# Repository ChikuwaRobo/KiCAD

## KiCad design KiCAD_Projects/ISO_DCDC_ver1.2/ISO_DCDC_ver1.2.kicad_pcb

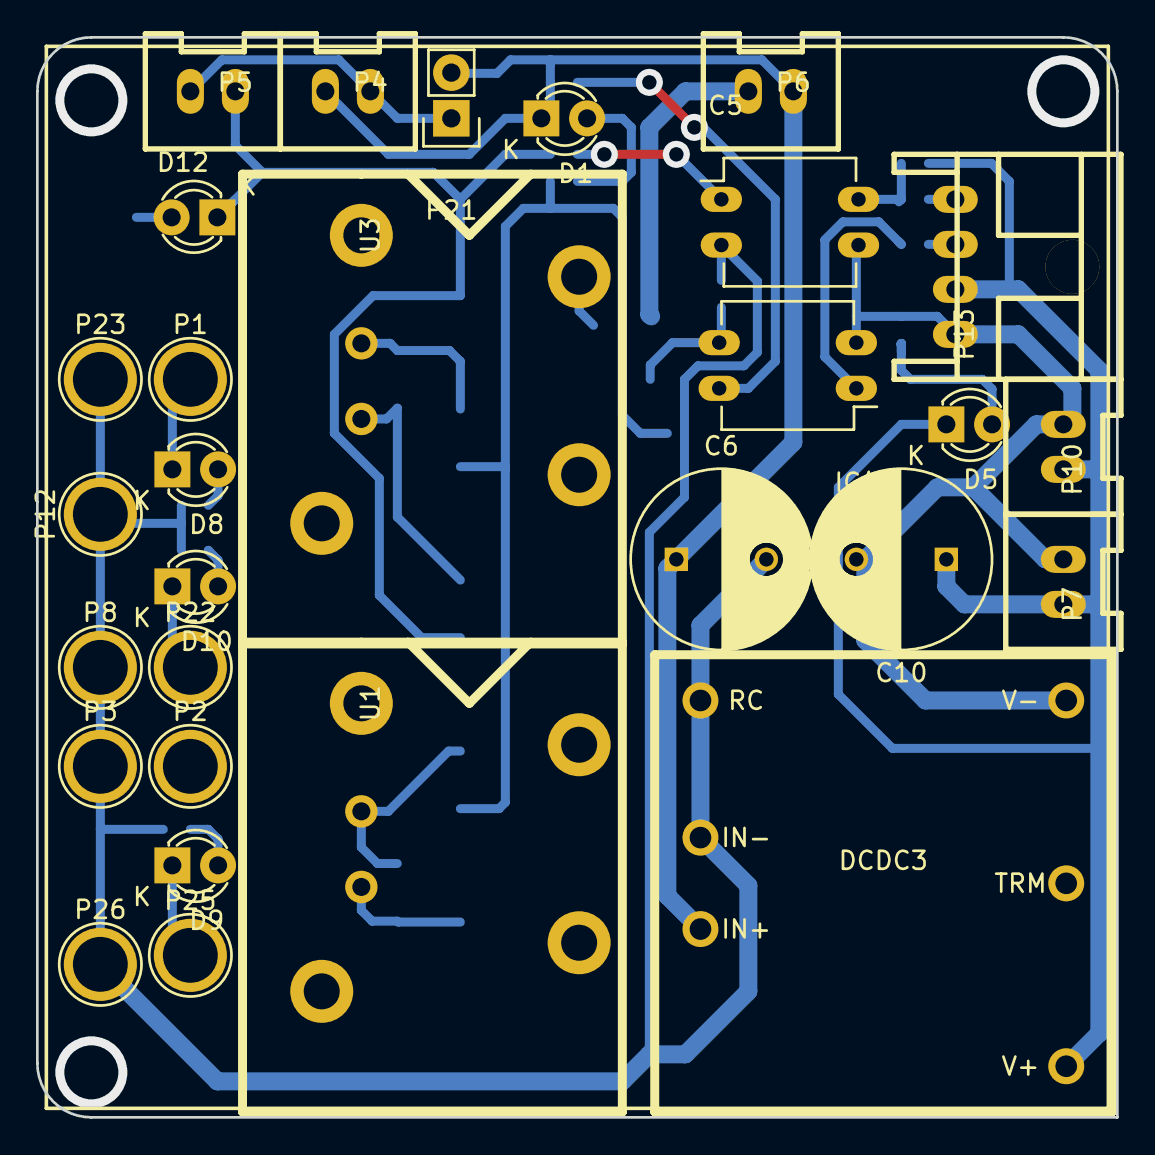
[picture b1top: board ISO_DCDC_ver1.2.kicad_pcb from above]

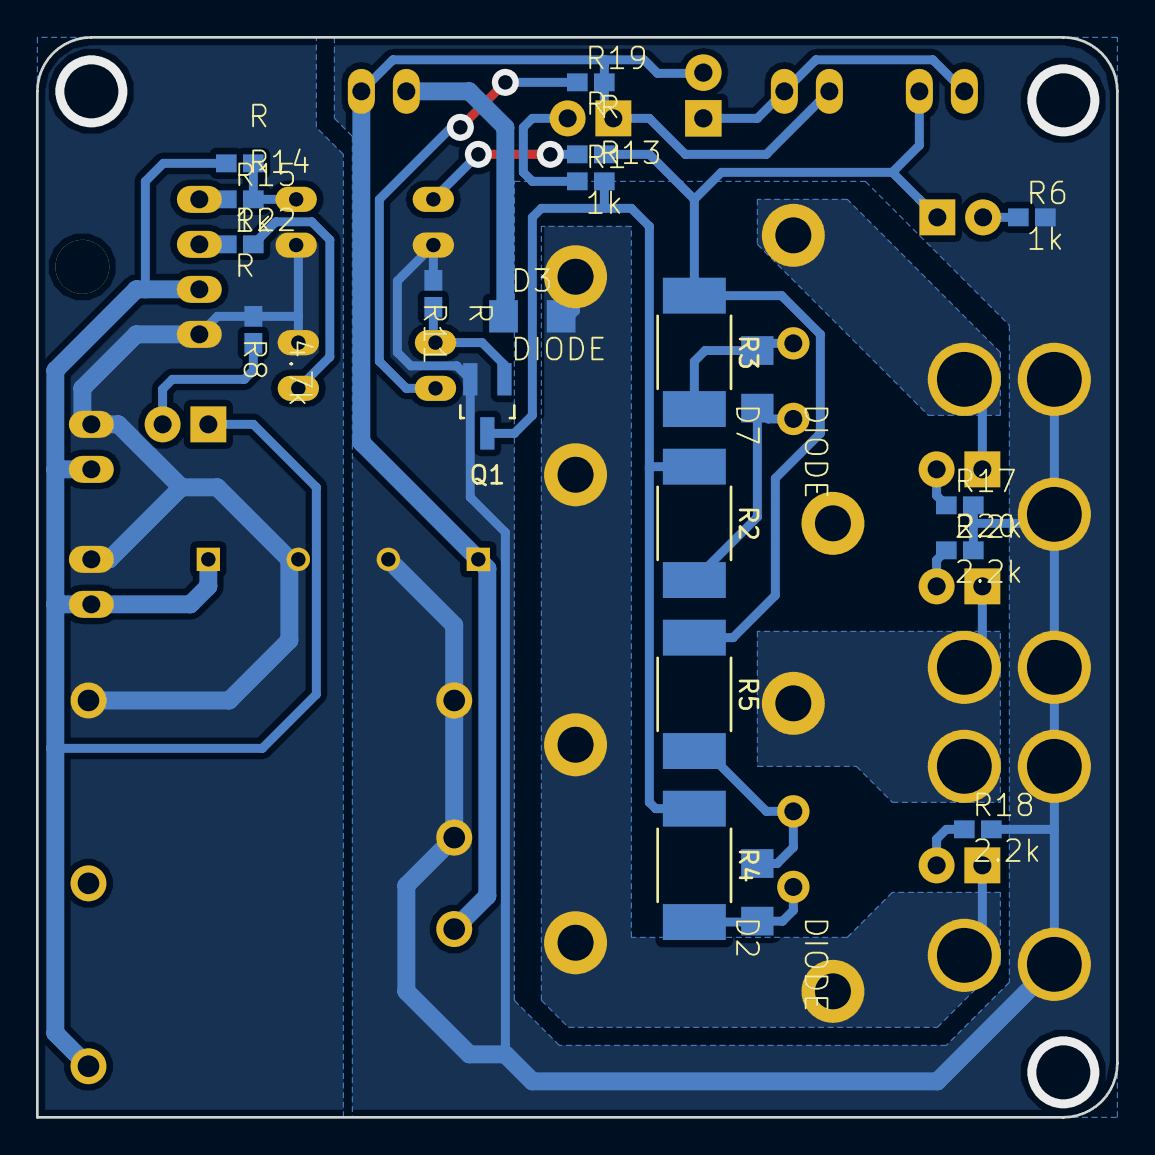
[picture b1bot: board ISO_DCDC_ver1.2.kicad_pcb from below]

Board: 2 copper layers, 60.0 x 60.0 mm, 49 parts (20 on the bottom side), 28 nets.

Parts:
C6, C10: 1000u; C_Radial_D10_L20_P5
D1, D5, D8, D9, D10, D12: LED; LED-3MM
D2, D3, D7: DIODE; C3216
DCDC3: MGS15
IC4, IC5: PC817; DIP-4_W7.62mm_LongPads_Slim
P1, P2, P3, P8, P12, P22, P23, P25, P26: CONN_01X01; 1pin
P4, P5, P6, P7, P10: CONN_01X02; XA_2T
P13: CONN_01X04; XA_4LC
P21: CONN_01X02; Pin_Header_Straight_1x02
Q1: MOSFET_N; SOT-23_Handsoldering
R1, R6, R15: 1k; C1608_NP
R2, R3, R4, R5: R; R_2812
R8: 4.7k; C1608_NP
R11, R13, R14, R19, R22: R; C1608_NP
R17, R18, R20: 2.2k; C1608_NP
U1, U3: V23076-D3001-D142; V23076-A3001-D142

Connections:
+BATT: D3.2, D9.1, P25.1, U1.4, U3.4
/12V: C10.1, D5.1, DCDC3.1, P7.2, P10.2, P13.2, R14.2
/15V: C6.1, D1.1, DCDC3.6, P4.1, P6.2, P21.2, R19.2
/POWER_EN_HIGH: D12.1, P5.2, R3.1, R5.1, R13.1
/POWER_EN_LOW: Q1.D, R1.2, R2.1, R4.1
GND: C10.2, DCDC3.3, IC4.2, IC5.3, P7.1, P10.1, P13.1, R8.2
GNDPWR: C6.2, DCDC3.4, DCDC3.5, IC5.2, P3.1, P8.1, P12.1, P23.1, P26.1, Q1.S, R6.2, R11.2, R17.2, R18.2, R20.2
unnamed: D1.2, R1.1
unnamed: D2.1, R4.2, U1.2
unnamed: D2.2, R5.2, U1.1
unnamed: D3.1, P6.1
unnamed: D5.2, R8.1
unnamed: D7.1, R2.2, U3.2
unnamed: D7.2, R3.2, U3.1
unnamed: D8.1, P1.1, U3.5
unnamed: D8.2, R17.1
unnamed: D9.2, R18.1
unnamed: D10.1, P2.1, P22.1, U1.5
unnamed: D10.2, R20.1
unnamed: D12.2, R6.1
unnamed: IC4.1, R22.2
unnamed: IC4.3, Q1.G, R11.1
unnamed: IC4.4, R19.1
unnamed: IC5.1, R13.2
unnamed: IC5.4, R14.1, R15.2
unnamed: P13.3, R22.1
unnamed: P13.4, R15.1
unnamed: P4.2, P5.1, P21.1

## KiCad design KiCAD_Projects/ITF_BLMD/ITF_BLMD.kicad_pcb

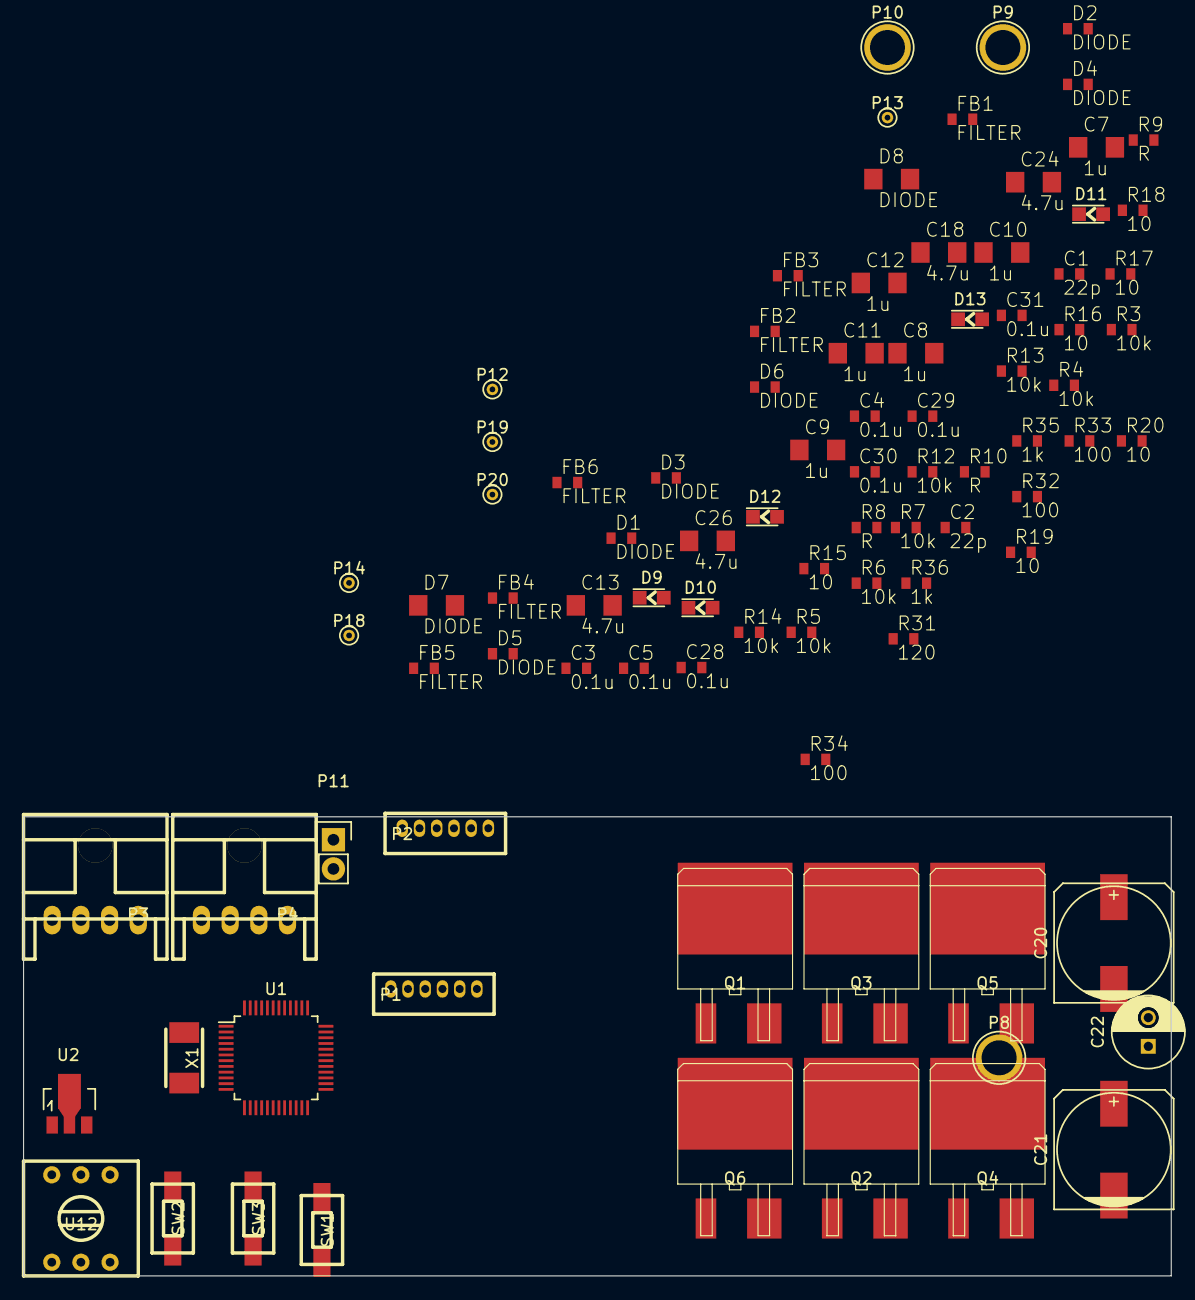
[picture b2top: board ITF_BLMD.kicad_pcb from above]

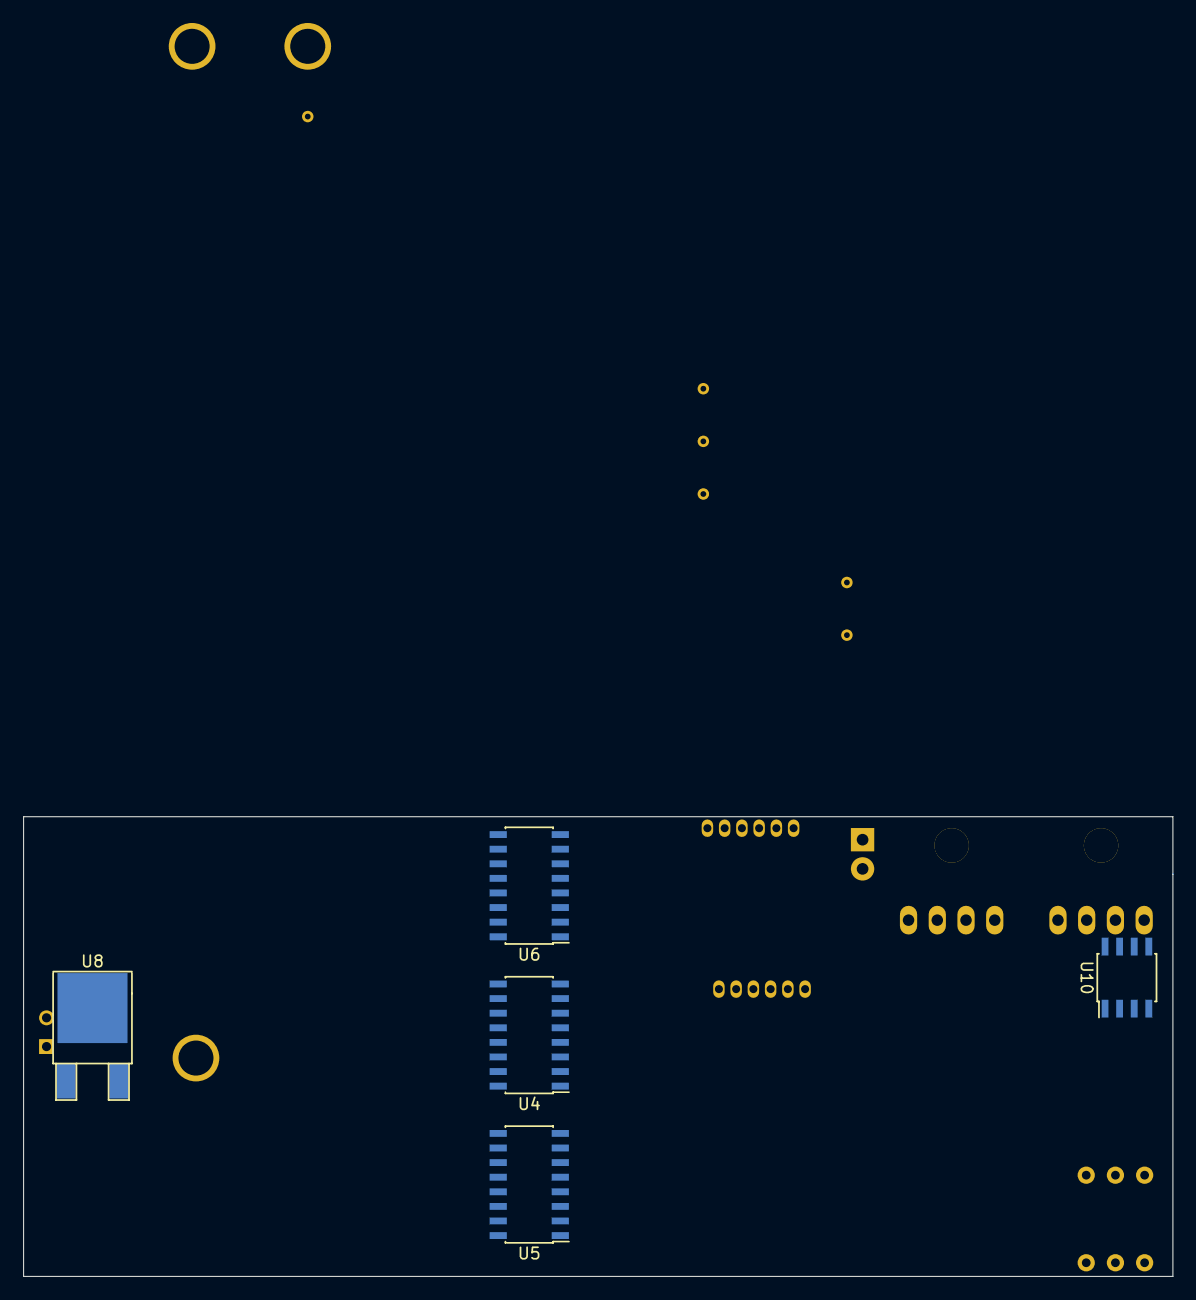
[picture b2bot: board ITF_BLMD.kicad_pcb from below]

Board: 2 copper layers, 100.0 x 40.0 mm, 96 parts (5 on the bottom side), 74 nets, no tracks yet.

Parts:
C1, C2: 22p; C1608_WP
C3, C4, C5, C28, C29, C30, C31: 0.1u; C1608_WP
C7, C8, C9, C10, C11, C12: 1u; C3216
C13, C18, C24, C26: 4.7u; C3216
C20, C21: 470u; c_elec_10x10.5
C22: 100u; C_Radial_D6.3_L11.2_P2.5
D1, D2, D3, D4, D5, D6: DIODE; C1608_WP
D7, D8: DIODE; C3216
D9, D10, D11, D12, D13: LED; LED_0805
FB1, FB2, FB3, FB4, FB5, FB6: FILTER; C1608_WP
P1, P2: CONN_01X06; ZH_6T
P3, P4: CONN_01X04; XA_4LC
P8, P9, P10: CONN_01X01; 1pin
P11: CONN_01X02; Pin_Header_Straight_1x02
P12, P13, P14, P18, P19, P20: CONN_01X01; PINTST
Q1, Q2, Q3, Q4, Q5, Q6: MOSFET_N; D2-PAK_compact
R3, R4, R5, R6, R7, R12, R13, R14: 10k; C1608_WP
R8, R9, R10: R; C1608_WP
R15, R16, R17, R18, R19, R20: 10; C1608_WP
R31: 120; C1608_WP
R32, R33, R34: 100; C1608_WP
R35, R36: 1k; C1608_WP
SW1, SW2, SW3: SW_PUSH; RP_SMD_Button
U1: STM32F103_48; LQFP-48_7x7mm_Pitch0.5mm
U2: NCP1117ST33T3G; SOT89-3_Housing
U4, U5, U6: SI8234; SOIC-16_3.9x9.9mm_Pitch1.27mm
U8: LM7812ACT; TO-252-2Lead
U10: MAX3051; SOIC-8_3.9x4.9mm_Pitch1.27mm
U12: SW_ROTARY_16; rotary_0F
X1: CRYSTAL; ABM3_2pads

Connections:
+3.3V: C3.1, C4.1, C5.1, C26.1, C28.1, C29.1, C30.1, C31.1, D9.1, P1.2, R6.1, U1.1, U1.9, U1.24, U1.36, U1.48, U2.2, U4.3, U4.8, U5.3, U5.8, U6.3, U6.8, U10.3
+5V: P2.6, R3.1, R4.1, R5.1
+12V: D8.2, D12.1, P3.2, P4.2
+BATT: C20.1, C21.1, D7.2, Q1.D, Q3.D, Q5.D
/BOOT0: R7.1, U1.44
/CAN_H: P3.3, P4.3, R31.2, U10.7
/CAN_L: P3.4, P4.4, P11.1, U10.6
/CAN_RX: U1.32, U10.4
/CAN_TX: U1.33, U10.1
/EN_U: U1.14, U4.5
/EN_V: U1.13, U5.5
/EN_W: U1.15, U6.5
/GD_12V: C18.1, D13.1, R15.1, R16.1, R17.1, R18.1, R19.1, R20.1, U8.3
/HALL_0: P2.2, P12.1, R3.2, U1.38
/HALL_1: P2.3, P13.1, R4.2, U1.39
/HALL_2: P2.4, P14.1, R5.2, U1.40
/LED_A: D10.1, U1.42
/LED_B: D11.1, U1.41
/NRST: R6.2, SW1.2, U1.7
/OUT_U: C7.2, P8.1, Q1.S, Q2.D, U4.14
/OUT_V: C9.2, P9.1, Q3.S, Q4.D, U5.14
/OUT_W: C11.2, P10.1, Q5.S, Q6.D, U6.14
/PWM_U: P20.1, U1.17, U4.1
/PWM_V: P18.1, U1.16, U5.1
/PWM_W: P19.1, U1.18, U6.1
/SEL_1: U1.4, U12.3
/SEL_2: U1.3, U12.1
/SEL_4: U1.46, U12.4
/SEL_8: U1.2, U12.6
/SW1: SW2.2, U1.43
/SW2: SW3.2, U1.45
/SWCLK: P1.3, U1.37
/SWDIO: P1.4, U1.34
/USART_RX: P1.6, U1.31
/USART_TX: P1.5, U1.30
GND: C1.1, C2.1, C3.2, C4.2, C5.2, C24.2, C26.2, C28.2, C29.2, C30.2, C31.2, P1.1, P2.1, P3.1, P4.1, R7.2, R8.2, R9.2, R10.2, R32.2, R33.2, R34.2, R35.2, SW1.1, SW2.1, SW3.1, U1.8, U1.23, U1.35, U1.47, U2.1, U4.4, U5.4, U6.4, U10.2, U10.5, U10.8, U12.2, U12.5
GNDPWR: C8.2, C10.2, C12.2, C13.2, C18.2, C20.2, C21.2, C22.2, Q2.S, Q4.S, Q6.S, R12.1, R13.1, R14.1, R36.2, U4.9, U5.9, U6.9, U8.2
unnamed: C1.2, U1.5, X1.1
unnamed: C2.2, U1.6, X1.2
unnamed: C7.1, D1.1, U4.16
unnamed: C8.1, D2.1, U4.11
unnamed: C9.1, D3.1, U5.16
unnamed: C10.1, D4.1, U5.11
unnamed: C11.1, D5.1, U6.16
unnamed: C12.1, D6.1, U6.11
unnamed: C13.1, C22.1, D7.1, U8.1
unnamed: C24.1, D8.1, U2.3
unnamed: D1.2, R15.2
unnamed: D2.2, R16.2
unnamed: D3.2, R17.2
unnamed: D4.2, R18.2
unnamed: D5.2, R19.2
unnamed: D6.2, R20.2
unnamed: D9.2, R32.1
unnamed: D10.2, R33.1
unnamed: D11.2, R34.1
unnamed: D12.2, R35.1
unnamed: D13.2, R36.1
unnamed: FB1.1, U4.15
unnamed: FB1.2, Q1.G
unnamed: FB2.1, R12.2, U4.10
unnamed: FB2.2, Q2.G
unnamed: FB3.1, U5.15
unnamed: FB3.2, Q3.G
unnamed: FB4.1, R13.2, U5.10
unnamed: FB4.2, Q4.G
unnamed: FB5.1, U6.15
unnamed: FB5.2, Q5.G
unnamed: FB6.1, R14.2, U6.10
unnamed: FB6.2, Q6.G
unnamed: P11.2, R31.1
unnamed: R8.1, U4.6
unnamed: R9.1, U5.6
unnamed: R10.1, U6.6
